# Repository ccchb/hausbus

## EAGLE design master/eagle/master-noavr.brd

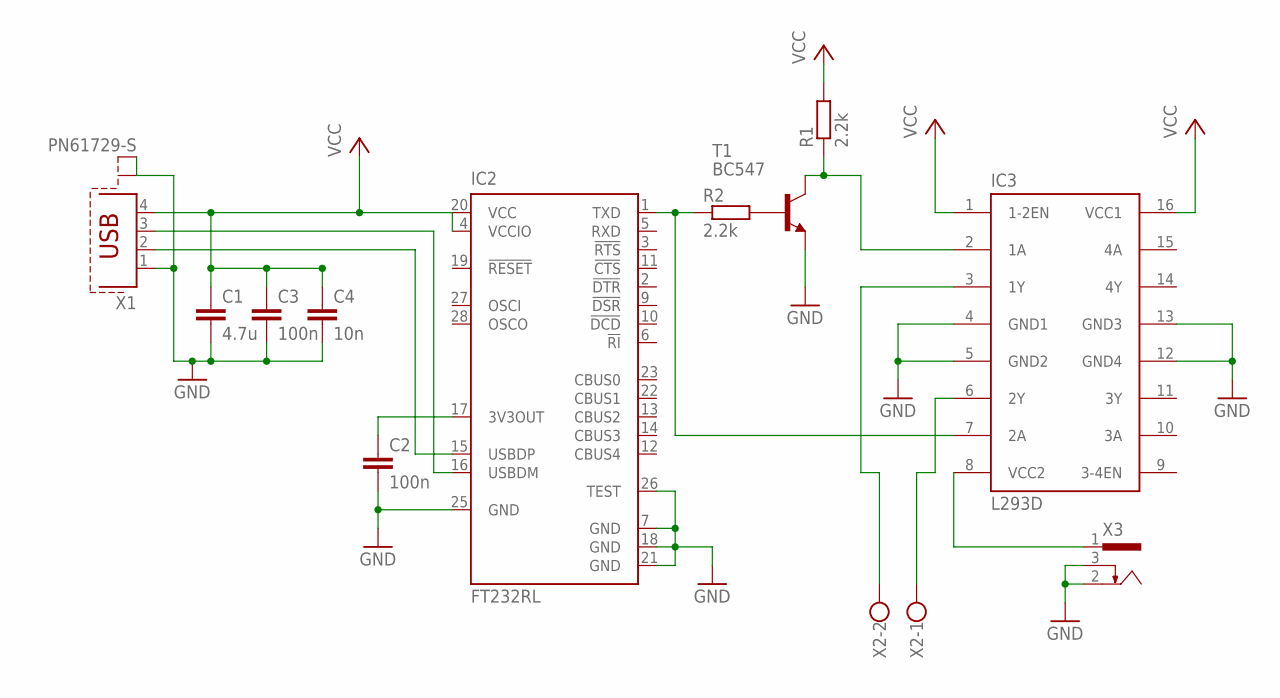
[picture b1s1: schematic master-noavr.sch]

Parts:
C1: 4.7u; C025-025X050
C2, C3: 100n; C025-025X050
C4: 10n; C025-025X050
IC2: FT232RL; SSOP28
IC3: L293D; DIL16
R1, R2: 2.2k; 0309/10
T1: BC547; TO92
X1: PN61729-S
X2: W237-102
X3: 733980-62

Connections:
GND: C1.2, C2.2, C3.2, C4.2, IC2.7 (GND), IC2.18 (GND), IC2.21 (GND), IC2.25 (GND), IC2.26 (TEST), IC3.4 (GND1), IC3.5 (GND2), IC3.12 (GND4), IC3.13 (GND3), T1.1 (E), X1.1, X1.S1, X1.S2, X3.2, X3.3
unnamed: IC2.1 (TXD), IC3.7 (2A), R2.1
unnamed: IC2.16 (USBDM), X1.3
unnamed: IC2.15 (USBDP), X1.2
unnamed: C2.1, IC2.17 (3V3OUT)
unnamed: R2.2, T1.2 (B)
unnamed: IC3.8 (VCC2), X3.1
unnamed: IC3.2 (1A), R1.1, T1.3 (C)
unnamed: IC3.3 (1Y), X2.2
unnamed: IC3.6 (2Y), X2.1
VCC: C1.1, C3.1, C4.1, IC2.4 (VCCIO), IC2.20 (VCC), IC3.1 (1-2EN), IC3.16 (VCC1), R1.2, X1.4

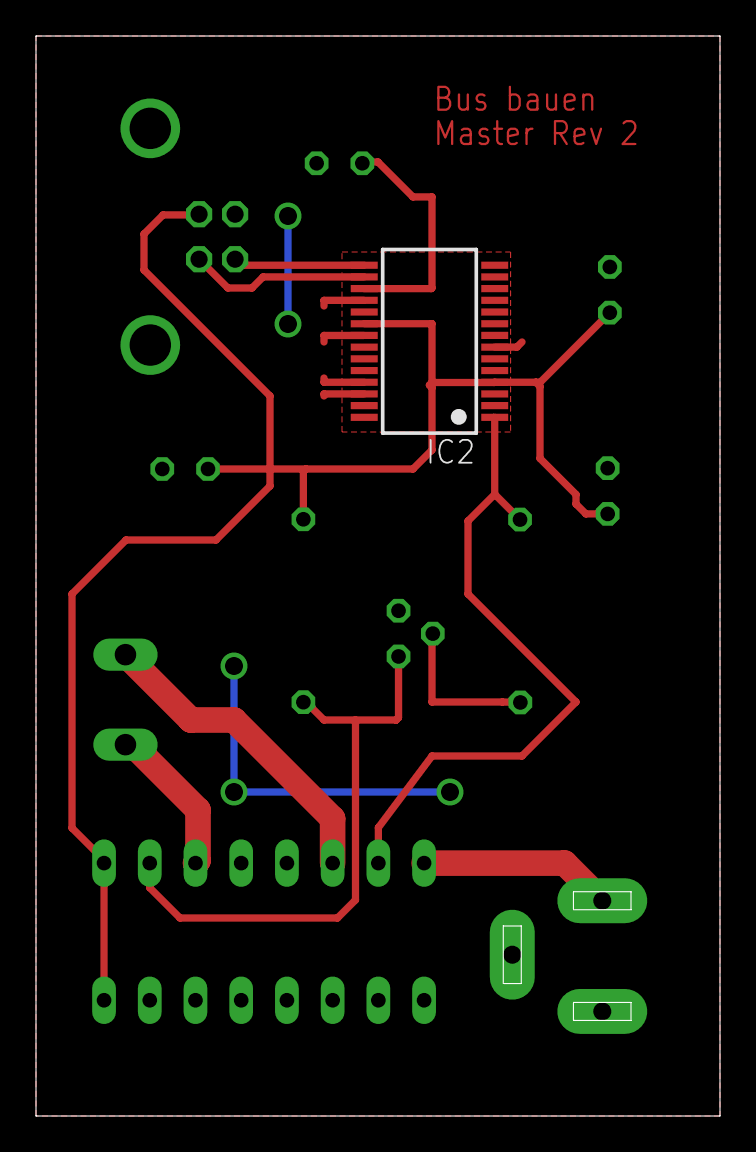
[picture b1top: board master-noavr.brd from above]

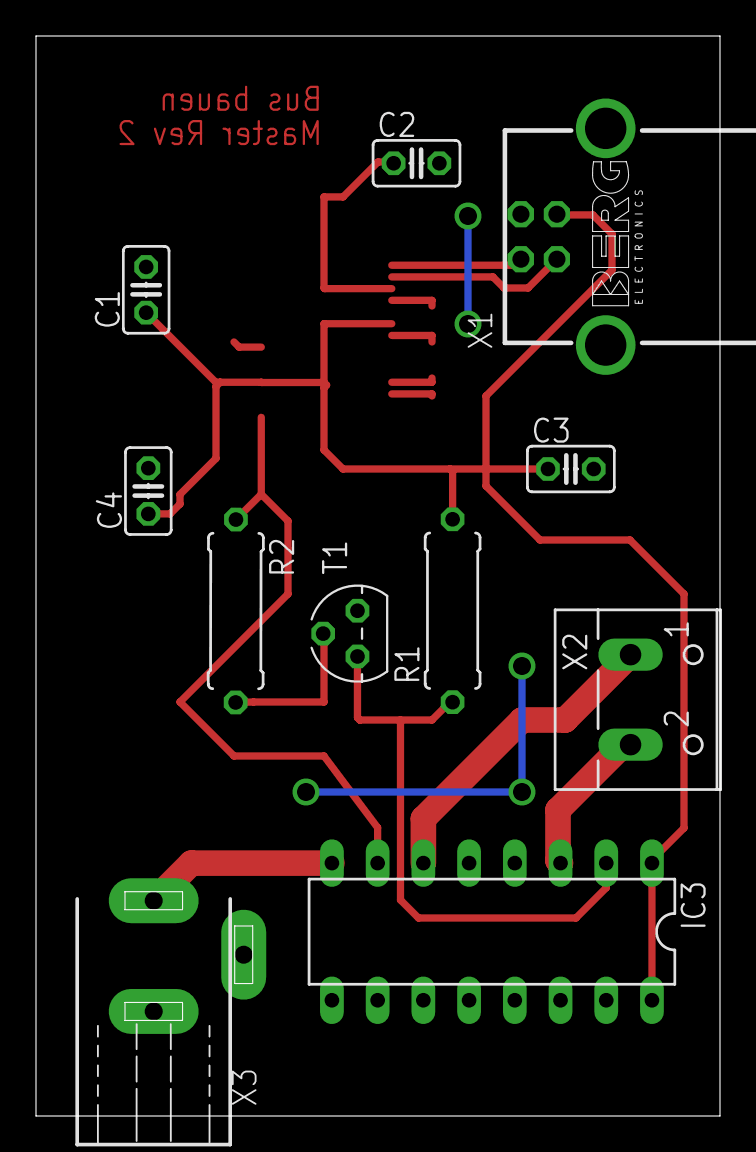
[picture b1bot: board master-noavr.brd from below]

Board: 2 copper layers, 38.0 x 60.0 mm, 12 parts (11 on the bottom side), 11 nets.

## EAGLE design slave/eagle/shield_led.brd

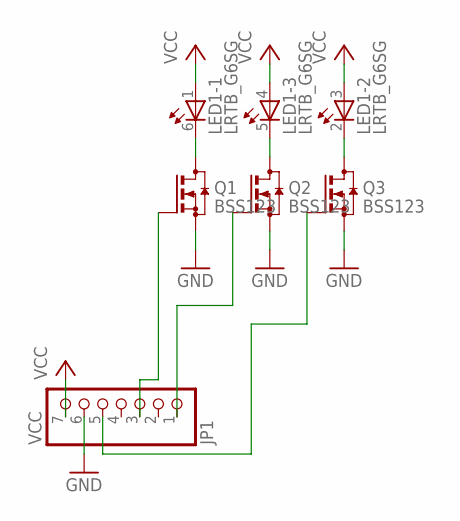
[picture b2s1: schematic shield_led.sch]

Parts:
JP1: VCC; 1X07
LED1: LRTB_G6SG
Q1, Q2, Q3: BSS123; SOT23

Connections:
GND: JP1.6, Q1.2 (S), Q2.2 (S), Q3.2 (S)
unnamed: LED1.6 (C), Q1.3 (D)
unnamed: LED1.2 (C), Q3.3 (D)
unnamed: LED1.5 (C), Q2.3 (D)
unnamed: JP1.3, Q1.1 (G)
unnamed: JP1.1, Q2.1 (G)
unnamed: JP1.5, Q3.1 (G)
VCC: JP1.7, LED1.1 (A), LED1.3 (A), LED1.4 (A)

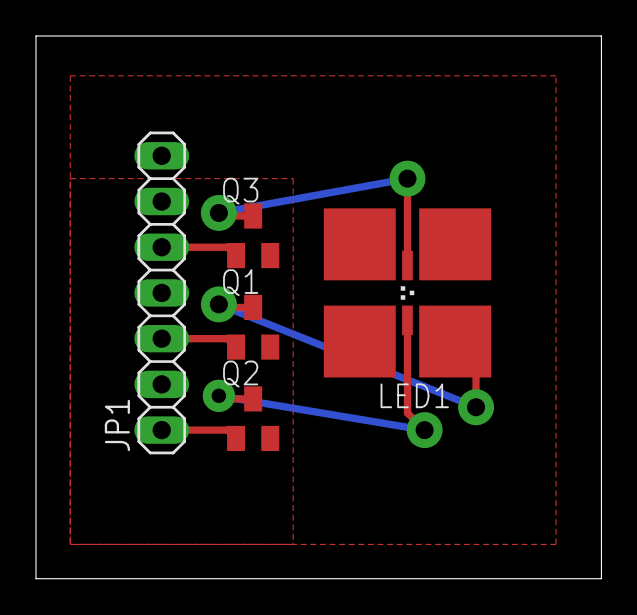
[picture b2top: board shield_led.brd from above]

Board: 2 copper layers, 31.4 x 30.1 mm, 5 parts (0 on the bottom side), 8 nets.

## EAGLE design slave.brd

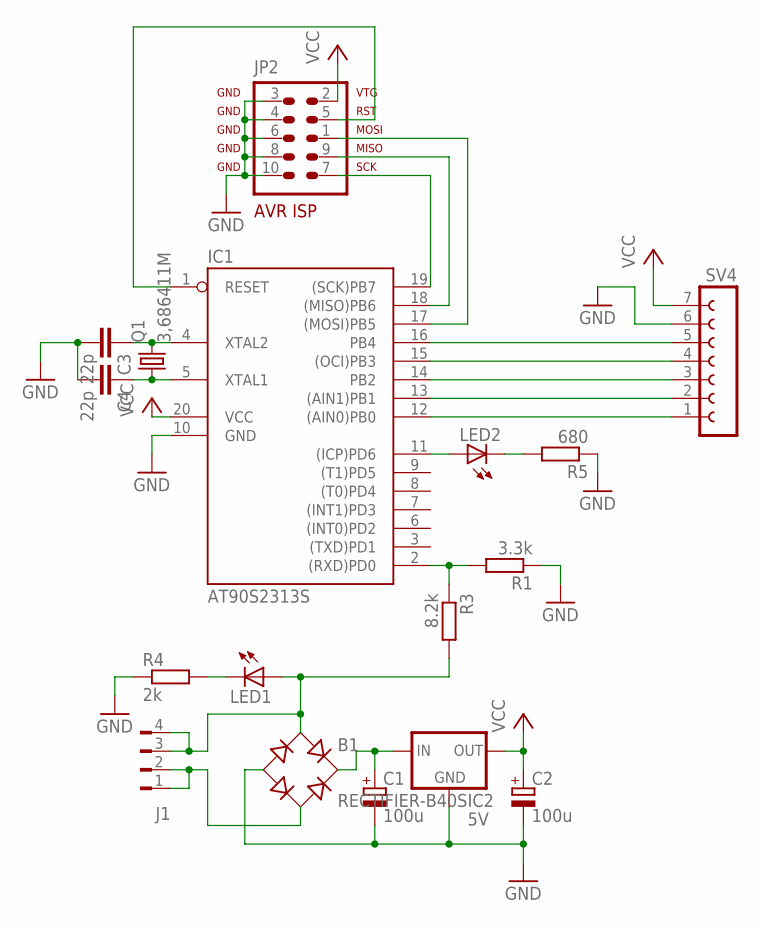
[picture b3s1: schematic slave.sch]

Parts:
B1: RECTIFIER-B40S; B40S
C1, C2: 100u; E2,5-6
C3, C4: 22p; C025-025X050
IC1: AT90S2313S; SO20L
IC2: 5V; 78XXS
J1: FLOPPY-4
JP2: AVR-ISP-10
LED1, LED2: LED3MM
Q1: 3,686411M; HC49U-V
R1: 3.3k; R1206W
R3: 8.2k; R1206W
R4: 2k; R1206W
R5: 680; R1206W
SV4: FE07-1; FE07

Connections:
GND: B1.-, C1.-, C2.-, C3.2, C4.2, IC1.10 (GND), IC2.GND, JP2.3, JP2.4, JP2.6, JP2.8, JP2.10, R1.1, R4.1, R5.1, SV4.6
unnamed: B1.+, C1.+, IC2.IN
unnamed: IC1.2 ((RXD)PD0), R1.2, R3.1
unnamed: LED1.K (C), R4.2
unnamed: IC1.11 ((ICP)PD6), LED2.A
unnamed: IC1.12 ((AIN0)PB0), SV4.1
unnamed: B1.AC1, J1.3, J1.4, LED1.A, R3.2
unnamed: C3.1, IC1.4 (XTAL2), Q1.2
unnamed: IC1.13 ((AIN1)PB1), SV4.2
unnamed: IC1.14 (PB2), SV4.3
unnamed: B1.AC2, J1.1, J1.2
unnamed: LED2.K (C), R5.2
unnamed: IC1.19 ((SCK)PB7), JP2.7
unnamed: IC1.18 ((MISO)PB6), JP2.9
unnamed: IC1.17 ((MOSI)PB5), JP2.1
unnamed: IC1.1 (RESET), JP2.5
unnamed: C4.1, IC1.5 (XTAL1), Q1.1
unnamed: IC1.15 ((OCI)PB3), SV4.4
unnamed: IC1.16 (PB4), SV4.5
VCC: C2.+, IC1.20 (VCC), IC2.OUT, JP2.2, SV4.7

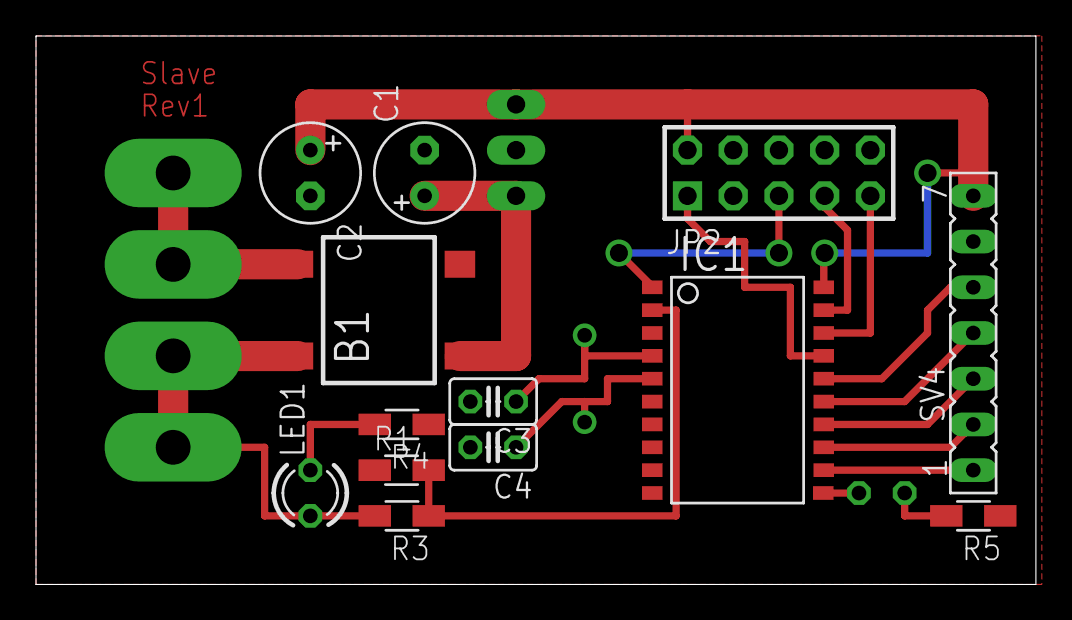
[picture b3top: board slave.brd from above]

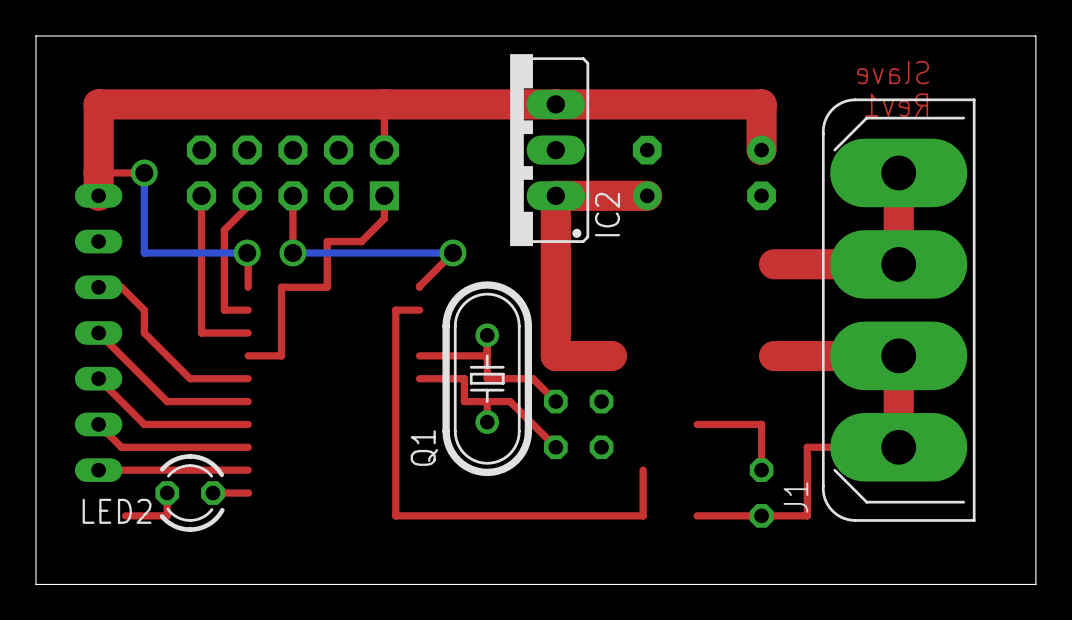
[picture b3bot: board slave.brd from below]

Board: 2 copper layers, 55.5 x 30.5 mm, 17 parts (4 on the bottom side), 20 nets.

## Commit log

2014-08-17 First etched and soldered board! And it even works!
2014-08-24 New directory structure + add slave state machine without any further logic
2014-08-30 Implement protocol + protocol documentation + C gitignore added
2014-08-30 led-shield: schema und board erstellt
2014-08-30 zzzzZZZZZzzzzzzzzZZZZZZZZZZ
2014-08-30 Makefile: überarbeitet
2014-08-30 slave: aktueller stand
2014-08-30 Add first approach on a master schematic + layout
2014-09-02 Protokolldoku angefangen
2014-09-02 protokoll: layer 2 dokumentiert
2014-09-02 proto.h: include guards
2014-09-04 new multi-target build system
2014-09-13 first master revision
2014-09-13 Yes, we already fixed the ground plane!
